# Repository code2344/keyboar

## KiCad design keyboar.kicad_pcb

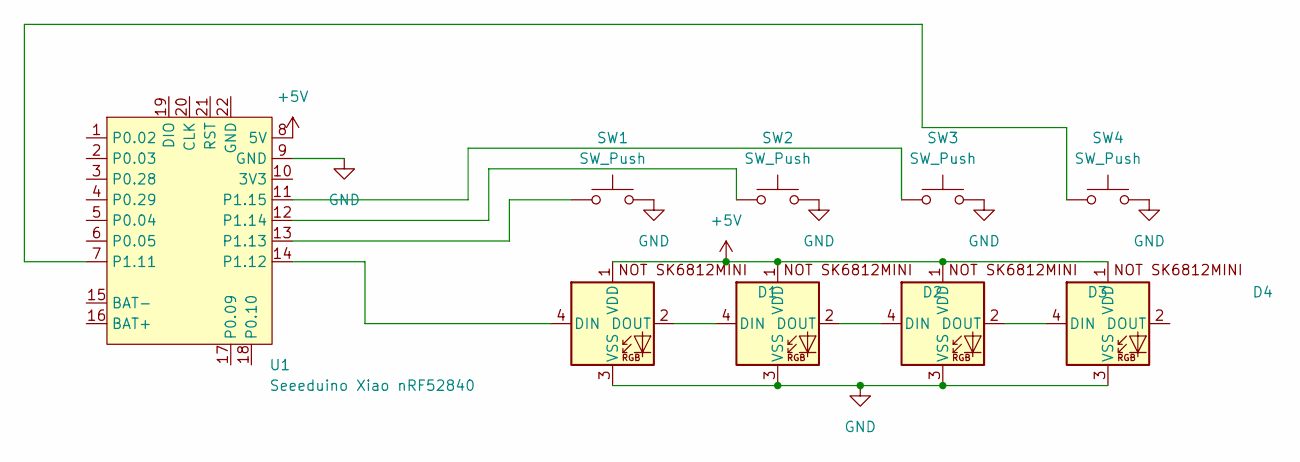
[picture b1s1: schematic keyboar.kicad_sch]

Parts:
D1, D2, D3, D4: SK6812MINI-E; LED_SK6812MINI_PLCC4_3.5x3.5mm_P1.75mm
SW1, SW2, SW3, SW4: SW_Push; SW_Cherry_MX_1.00u_PCB
U1: Seeeduino Xiao nRF52840; Xiao_nRF52840_ACH

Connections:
+5V: D1.1 (VDD), D2.1 (VDD), D3.1 (VDD), D4.1 (VDD), U1.8 (5V)
GND: D1.3 (VSS), D2.3 (VSS), D3.3 (VSS), D4.3 (VSS), SW1.2, SW2.2, SW3.2, SW4.2, U1.9 (GND)
unnamed: D1.4 (DIN), U1.14 (P1.12)
unnamed: D1.2 (DOUT), D2.4 (DIN)
unnamed: D2.2 (DOUT), D3.4 (DIN)
unnamed: D3.2 (DOUT), D4.4 (DIN)
unnamed: SW4.1, U1.7 (P1.11)
unnamed: SW1.1, U1.13 (P1.13)
unnamed: SW2.1, U1.12 (P1.14)
unnamed: SW3.1, U1.11 (P1.15)

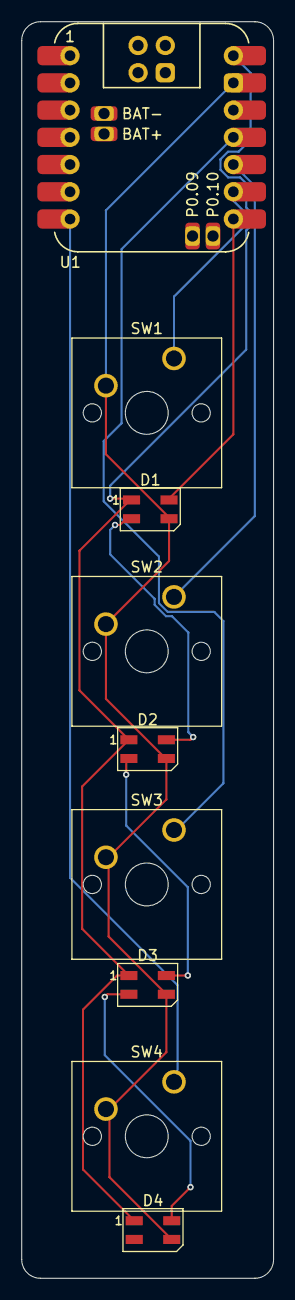
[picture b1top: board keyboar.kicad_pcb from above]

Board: 2 copper layers, 23.5 x 117.2 mm, 9 parts (0 on the bottom side), 10 nets.

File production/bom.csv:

Designator,Footprint,Quantity,Value,LCSC Part #
"D1, D2, D3, D4",LED_SK6812MINI_PLCC4_3.5x3.5mm_P1.75mm,4,SK6812MINI-E,
"SW1, SW2, SW3, SW4",SW_Cherry_MX_1.00u_PCB,4,SW_Push,

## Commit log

2026-05-21 full project commit
2026-05-21 remove random non maacos file
